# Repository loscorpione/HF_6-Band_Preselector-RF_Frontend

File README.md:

<h2 align="center">HF 6-Band Preselector – RF Frontend</h4>

This project is a 6-band HF RF preselector designed to improve the selectivity and dynamic performance of HF receivers, particularly homebrew and direct-conversion receivers.

The preselector covers the frequency range from 200 kHz to 30 MHz through six LC band-pass filters. The appropriate filter is selected automatically according to the band selected on the VFO.
The project was developed as an RF frontend for my ESP32 + Si5351 VFO/BFO, creating an integrated and automatically controlled RF signal chain.
In addition to the band-pass filters, the board includes a selectable 0 / -20 dB RF attenuator, controlled directly by the VFO.

<h2 align="center">🎬 Video del progetto</h2>

<p align="center">
  
</p>

<h2 align="center">📻 Frequency coverage</h2>
Filter	Frequency range	Main applications
1	0.2 – 1 MHz	Long Wave, Medium Wave, 630 m
2	1 – 2 MHz	Medium Wave, 160 m
3	2 – 4 MHz	80 m, 60 m
4	4 – 8 MHz	40 m, Short Wave
5	8 – 15 MHz	30 m, 20 m, Short Wave
6	15 – 30 MHz	17 m, 15 m, 12 m, 10 m, Short Wave

<h2 align="center">🔛Filter Switching</h2>

The six filters are selected using RF relays controlled by a CD4028 decoder and an ULN2003 Darlington transistor array.
The VFO sends the selected band information to the CD4028, which activates the corresponding output. The ULN2003 then drives the relay coil, allowing the correct RF filter to be connected.
This approach reduces the number of control lines required between the VFO and the RF frontend while keeping the RF switching section simple and reliable.

<h2 align="center">🛠️ Integrazione con il VFO/BFO</h2>

- [Mappatura delle uscite digitali per la selezione dei filtri](Mappatura-Uscite-Band.md)

<h2 align="center">📻 RF Attenuator</h2>

The board also includes a selectable 0 / -20 dB attenuator based on a 50 Ω resistive network.
The attenuator can be controlled directly from the VFO and can be useful when the receiver is overloaded by strong signals or out-of-band energy.

<h2 align="center">🔌 Testing</h2>

The filters were tested using a NanoVNA, measuring their frequency response, insertion loss and bandwidth.
The measured responses do not perfectly match the calculated values. The differences are most likely related to component tolerances, particularly the inductors.
Further adjustments to the filter component values are therefore planned to improve the correspondence between the calculated and measured responses.

<h2 align="center">🛠️ Hardware</h2>

The PCB was designed with particular attention to RF layout:

short RF tracks;
extensive ground plane;
physically separated filter sections;
relays positioned close to the RF paths;
50 Ω RF input and output;
dedicated filtering for each frequency range.
Status

Working prototype – further RF optimization planned.

<h2 align="center"></h2>

This repository contains the hardware design files, documentation and test information for the project.

<h2 align="center">⚠️ Disclaimer</h2>

This project is intended for educational, experimental and amateur-radio purposes.
RF circuits can behave differently depending on component tolerances, PCB construction, wiring, grounding and measurement equipment.
Always verify the circuit and its behavior before connecting it to valuable radio equipment.

<h2 align="center">📄 License</h2>

The licensing terms for this project are currently being finalized.
The original filter design is based on the work of Dian Kurniawan, which in turn references the work of Matti Hohtola (OH7SV).
Commercial use or commercial redistribution of this implementation is not authorized while the final licensing terms are being established.

ScorpioneMaker

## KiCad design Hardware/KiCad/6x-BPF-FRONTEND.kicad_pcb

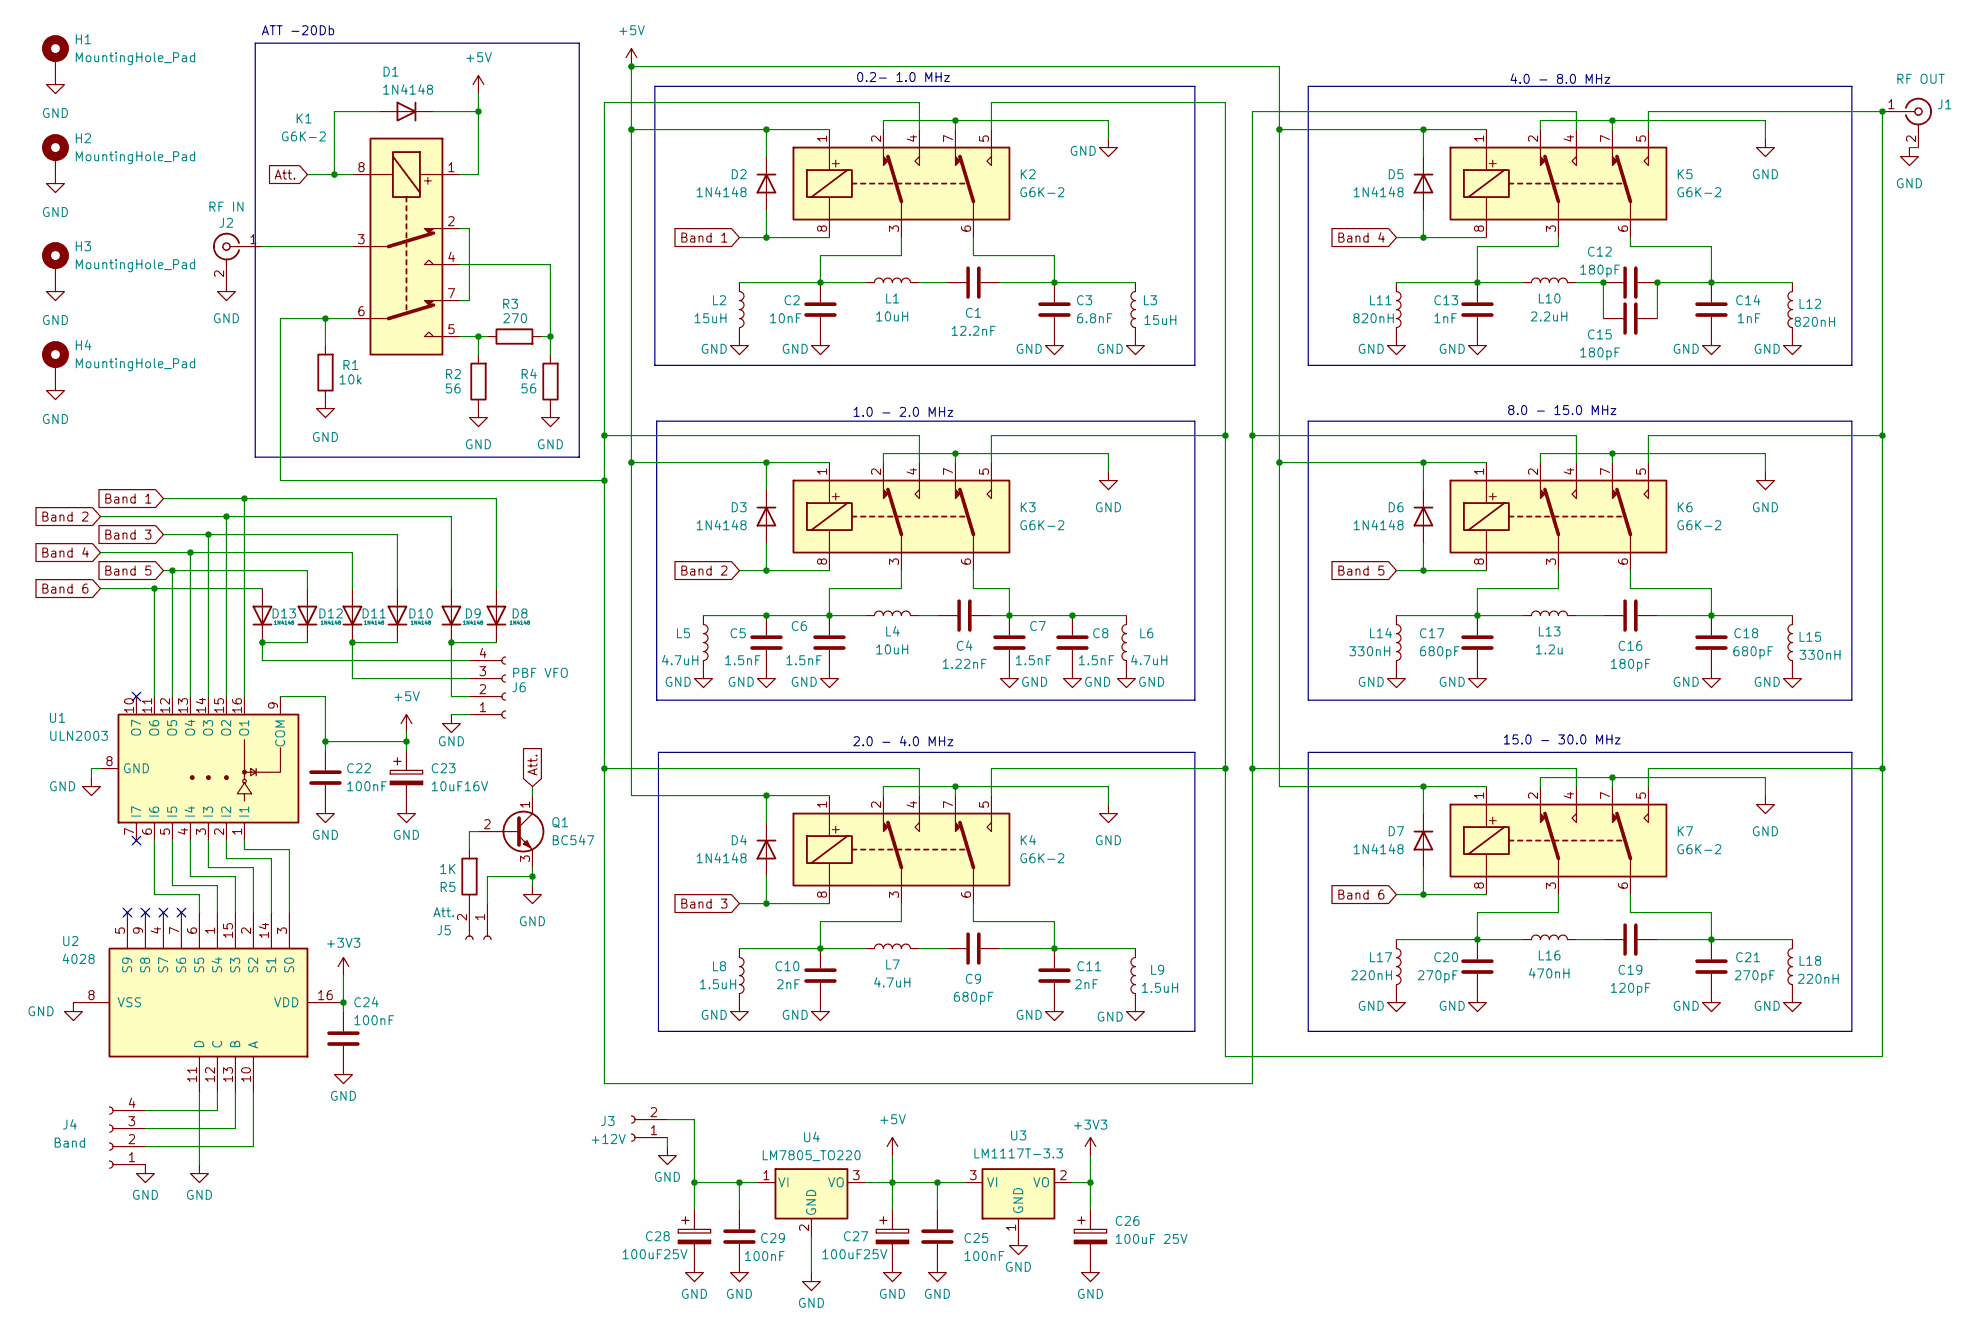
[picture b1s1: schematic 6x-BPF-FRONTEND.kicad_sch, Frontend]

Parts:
C1: 12.2nF; C_Disc_D6.0mm_W2.5mm_P5.00mm
C2: 10nF; C_Disc_D6.0mm_W2.5mm_P5.00mm
C3: 6.8nF; C_Disc_D6.0mm_W2.5mm_P5.00mm
C4: 1.22nF; C_Disc_D6.0mm_W2.5mm_P5.00mm
C5, C6, C7, C8: 1.5nF; C_Disc_D6.0mm_W2.5mm_P5.00mm
C9, C17, C18: 680pF; C_Disc_D6.0mm_W2.5mm_P5.00mm
C10, C11: 2nF; C_Disc_D6.0mm_W2.5mm_P5.00mm
C12, C15, C16: 180pF; C_Disc_D6.0mm_W2.5mm_P5.00mm
C13, C14: 1nF; C_Disc_D6.0mm_W2.5mm_P5.00mm
C19: 120pF; C_Disc_D6.0mm_W2.5mm_P5.00mm
C20, C21: 270pF; C_Disc_D6.0mm_W2.5mm_P5.00mm
C22, C24, C25, C29: 100nF; C_Rect_L7.0mm_W2.5mm_P5.00mm
C23: 10uF16V; CP_Radial_D4.0mm_P2.00mm
C26: 100uF 25V; CP_Radial_D7.5mm_P2.50mm
C27, C28: 100uF25V; CP_Radial_D7.5mm_P2.50mm
D1, D2, D3, D4, D5, D6, D7, D8, D9, D10, D11, D12, D13: 1N4148; D_DO-35_SOD27_P7.62mm_Horizontal
H1, H2, H3, H4: MountingHole_Pad; MountingHole_3.2mm_M3_DIN965_Pad
J1: RF OUT; SMA_Amphenol_901-144_Vertical
J2: RF IN; SMA_Amphenol_901-144_Vertical
J3: +12V; JST_XH_B2B-XH-A_1x02_P2.50mm_Vertical
J4: Band; JST_XH_B4B-XH-A_1x04_P2.50mm_Vertical
J5: Att.; JST_XH_B2B-XH-A_1x02_P2.50mm_Vertical
J6: PBF VFO; JST_XH_B4B-XH-A_1x04_P2.50mm_Vertical
K1, K2, K3, K4, K5, K6, K7: G6K-2; Relay_DPDT_Omron_G6K-2P-Y
L1, L4: 10uH; L_Axial_L7.0mm_D3.3mm_P10.16mm_Horizontal_Fastron_MICC
L2, L3: 15uH; L_Axial_L7.0mm_D3.3mm_P10.16mm_Horizontal_Fastron_MICC
L5, L6, L7: 4.7uH; L_Axial_L7.0mm_D3.3mm_P10.16mm_Horizontal_Fastron_MICC
L8, L9: 1.5uH; L_Axial_L7.0mm_D3.3mm_P10.16mm_Horizontal_Fastron_MICC
L10: 2.2uH; L_Axial_L7.0mm_D3.3mm_P10.16mm_Horizontal_Fastron_MICC
L11, L12: 820nH; L_Axial_L7.0mm_D3.3mm_P10.16mm_Horizontal_Fastron_MICC
L13: 1.2u; L_Axial_L7.0mm_D3.3mm_P10.16mm_Horizontal_Fastron_MICC
L14, L15: 330nH; L_Axial_L7.0mm_D3.3mm_P10.16mm_Horizontal_Fastron_MICC
L16: 470nH; L_Axial_L7.0mm_D3.3mm_P10.16mm_Horizontal_Fastron_MICC
L17, L18: 220nH; L_Axial_L7.0mm_D3.3mm_P10.16mm_Horizontal_Fastron_MICC
Q1: BC547; TO-92_Inline_Wide
R1: 10k; R_Axial_DIN0207_L6.3mm_D2.5mm_P10.16mm_Horizontal
R2, R4: 56; R_Axial_DIN0207_L6.3mm_D2.5mm_P10.16mm_Horizontal
R3: 270; R_Axial_DIN0207_L6.3mm_D2.5mm_P10.16mm_Horizontal
R5: 1K; R_Axial_DIN0207_L6.3mm_D2.5mm_P10.16mm_Horizontal
U1: ULN2003; DIP-16_W7.62mm
U2: 4028; DIP-16_W7.62mm
U3: LM1117T-3.3; TO-220-3_Vertical
U4: LM7805_TO220; TO-220-3_Vertical

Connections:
+3V3: C24.1, C26.1, U2.16 (VDD), U3.2 (VO)
+5V: C22.1, C23.1, C25.1, C27.1, D1.1 (K), D2.1 (K), D3.1 (K), D4.1 (K), D5.1 (K), D6.1 (K), D7.1 (K), K1.1, K2.1, K3.1, K4.1, K5.1, K6.1, K7.1, U1.9 (COM), U3.3 (VI), U4.3 (VO)
Att.: D1.2 (A), K1.8, Q1.1 (C)
Band 1: D2.2 (A), D8.2 (A), K2.8, U1.16 (O1)
Band 2: D3.2 (A), D9.2 (A), K3.8, U1.15 (O2)
Band 3: D4.2 (A), D10.2 (A), K4.8, U1.14 (O3)
Band 4: D5.2 (A), D11.2 (A), K5.8, U1.13 (O4)
Band 5: D6.2 (A), D12.2 (A), K6.8, U1.12 (O5)
Band 6: D7.2 (A), D13.2 (A), K7.8, U1.11 (O6)
GND: C2.2, C3.2, C5.2, C6.2, C7.2, C8.2, C10.2, C11.2, C13.2, C14.2, C17.2, C18.2, C20.2, C21.2, C22.2, C23.2, C24.2, C25.2, C26.2, C27.2, C28.2, C29.2, H1.1, H2.1, H3.1, H4.1, J1.2 (Ext), J2.2 (Ext), J3.1, J4.1, J5.1, J6.1, K2.2, K2.7, K3.2, K3.7, K4.2, K4.7, K5.2, K5.7, K6.2, K6.7, K7.2, K7.7, L2.2, L3.2, L5.2, L6.2, L8.2, L9.2, L11.2, L12.2, L14.2, L15.2, L17.2, L18.2, Q1.3 (E), R1.1, R2.1, R4.1, U1.8 (GND), U2.8 (VSS), U2.11 (D), U3.1 (GND), U4.2 (GND); also elsewhere on the board
unnamed: C1.1, C3.1, K2.6, L3.1
unnamed: C1.2, L1.2
unnamed: C2.1, K2.3, L1.1, L2.1
unnamed: C4.1, C7.1, C8.1, K3.6, L6.1
unnamed: C4.2, L4.2
unnamed: C5.1, C6.1, K3.3, L4.1, L5.1
unnamed: C9.2, L7.2
unnamed: C10.1, K4.3, L7.1, L8.1
unnamed: C9.1, C11.1, K4.6, L9.1
unnamed: C12.1, C14.1, C15.1, K5.6, L12.1
unnamed: C12.2, C15.2, L10.2
unnamed: C13.1, K5.3, L10.1, L11.1
unnamed: C16.1, C18.1, K6.6, L15.1
unnamed: C16.2, L13.2
unnamed: C17.1, K6.3, L13.1, L14.1
unnamed: C19.1, C21.1, K7.6, L18.1
unnamed: C19.2, L16.2
unnamed: C20.1, K7.3, L16.1, L17.1
unnamed 28: D8.1 (K), D9.1 (K), J6.2; also elsewhere on the board
unnamed 29: D10.1 (K), D11.1 (K), J6.3; also elsewhere on the board
unnamed 30: D12.1 (K), D13.1 (K), J6.4; also elsewhere on the board
unnamed 31: J1.1 (In), K2.5, K3.5, K4.5, K5.5, K6.5, K7.5; also elsewhere on the board
unnamed 32: J2.1 (In), K1.3; also elsewhere on the board
unnamed 33: C28.1, C29.1, J3.2, U4.1 (VI); also elsewhere on the board
unnamed 34: J4.2, U2.10 (A); also elsewhere on the board
unnamed 35: J4.3, U2.13 (B); also elsewhere on the board
unnamed 36: J4.4, U2.12 (C); also elsewhere on the board
unnamed 37: J5.2, R5.1; also elsewhere on the board
unnamed: K1.2, K1.7
unnamed: K1.4, R3.2, R4.2
unnamed: K1.5, R2.2, R3.1
unnamed: K1.6, K2.4, K3.4, K4.4, K5.4, K6.4, K7.4, R1.2
unnamed: Q1.2 (B), R5.2
unnamed: U1.1 (I1), U2.3 (S0)
unnamed: U1.2 (I2), U2.14 (S1)
unnamed: U1.3 (I3), U2.2 (S2)
unnamed: U1.4 (I4), U2.15 (S3)
unnamed: U1.5 (I5), U2.1 (S4)
unnamed: U1.6 (I6), U2.6 (S5)

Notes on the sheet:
2.0 - 4.0 MHz
1.0 - 2.0 MHz
8.0 - 15.0 MHz
0.2- 1.0 MHz
4.0 - 8.0 MHz
ATT -20Db
15.0 - 30.0 MHz

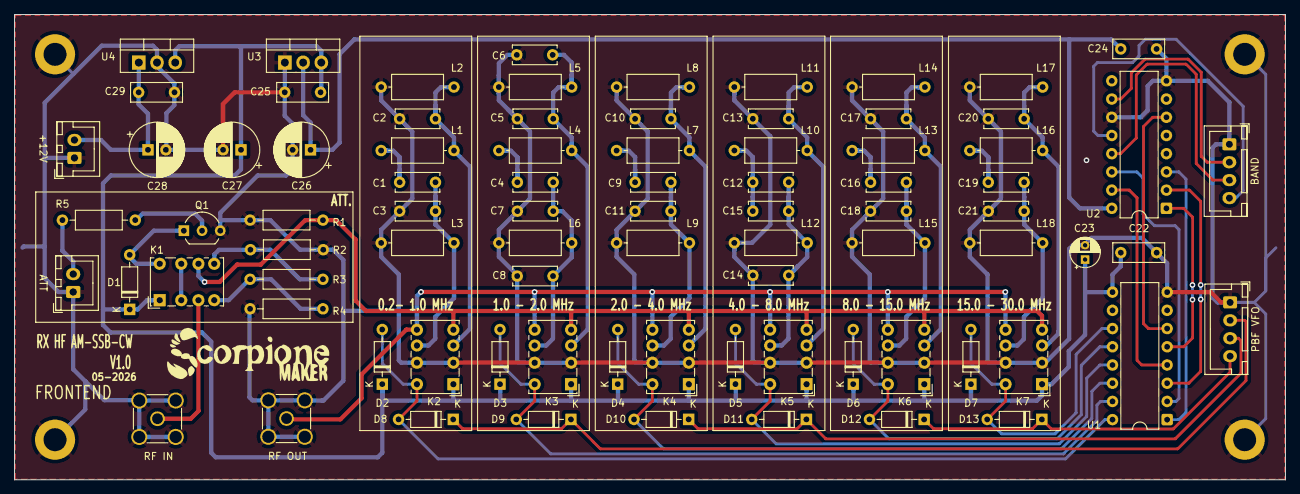
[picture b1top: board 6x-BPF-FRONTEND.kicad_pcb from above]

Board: 2 copper layers, 177.3 x 64.9 mm, 87 parts (0 on the bottom side), 49 nets.

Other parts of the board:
+12V: +12V; JST_XH_B2B-XH-A_1x02_P2.50mm_Vertical
ATT: Att.; JST_XH_B2B-XH-A_1x02_P2.50mm_Vertical
BAND : Band; JST_XH_B4B-XH-A_1x04_P2.50mm_Vertical
PBF VFO: PBF VFO; JST_XH_B4B-XH-A_1x04_P2.50mm_Vertical
RF IN: Ant. IN; SMA_Amphenol_901-144_Vertical
RF OUT: RF OUT; SMA_Amphenol_901-144_Vertical

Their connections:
GND: +12V.1, ATT.1, BAND.1, PBF VFO.1, RF IN.2 (Ext), RF OUT.2 (Ext); also elsewhere on the board
unnamed 28: PBF VFO.2; also elsewhere on the board
unnamed 29: PBF VFO.3; also elsewhere on the board
unnamed 30: PBF VFO.4; also elsewhere on the board
unnamed 31: RF OUT.1 (In); also elsewhere on the board
unnamed 32: RF IN.1 (In); also elsewhere on the board
unnamed 33: +12V.2; also elsewhere on the board
unnamed 34: BAND.2; also elsewhere on the board
unnamed 35: BAND.3; also elsewhere on the board
unnamed 36: BAND.4; also elsewhere on the board
unnamed 37: ATT.2; also elsewhere on the board
